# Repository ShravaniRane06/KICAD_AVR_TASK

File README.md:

# KICAD_AVR_TASK
AVR Atmega328 IPD Task1
PCB AND SCHEMATIC

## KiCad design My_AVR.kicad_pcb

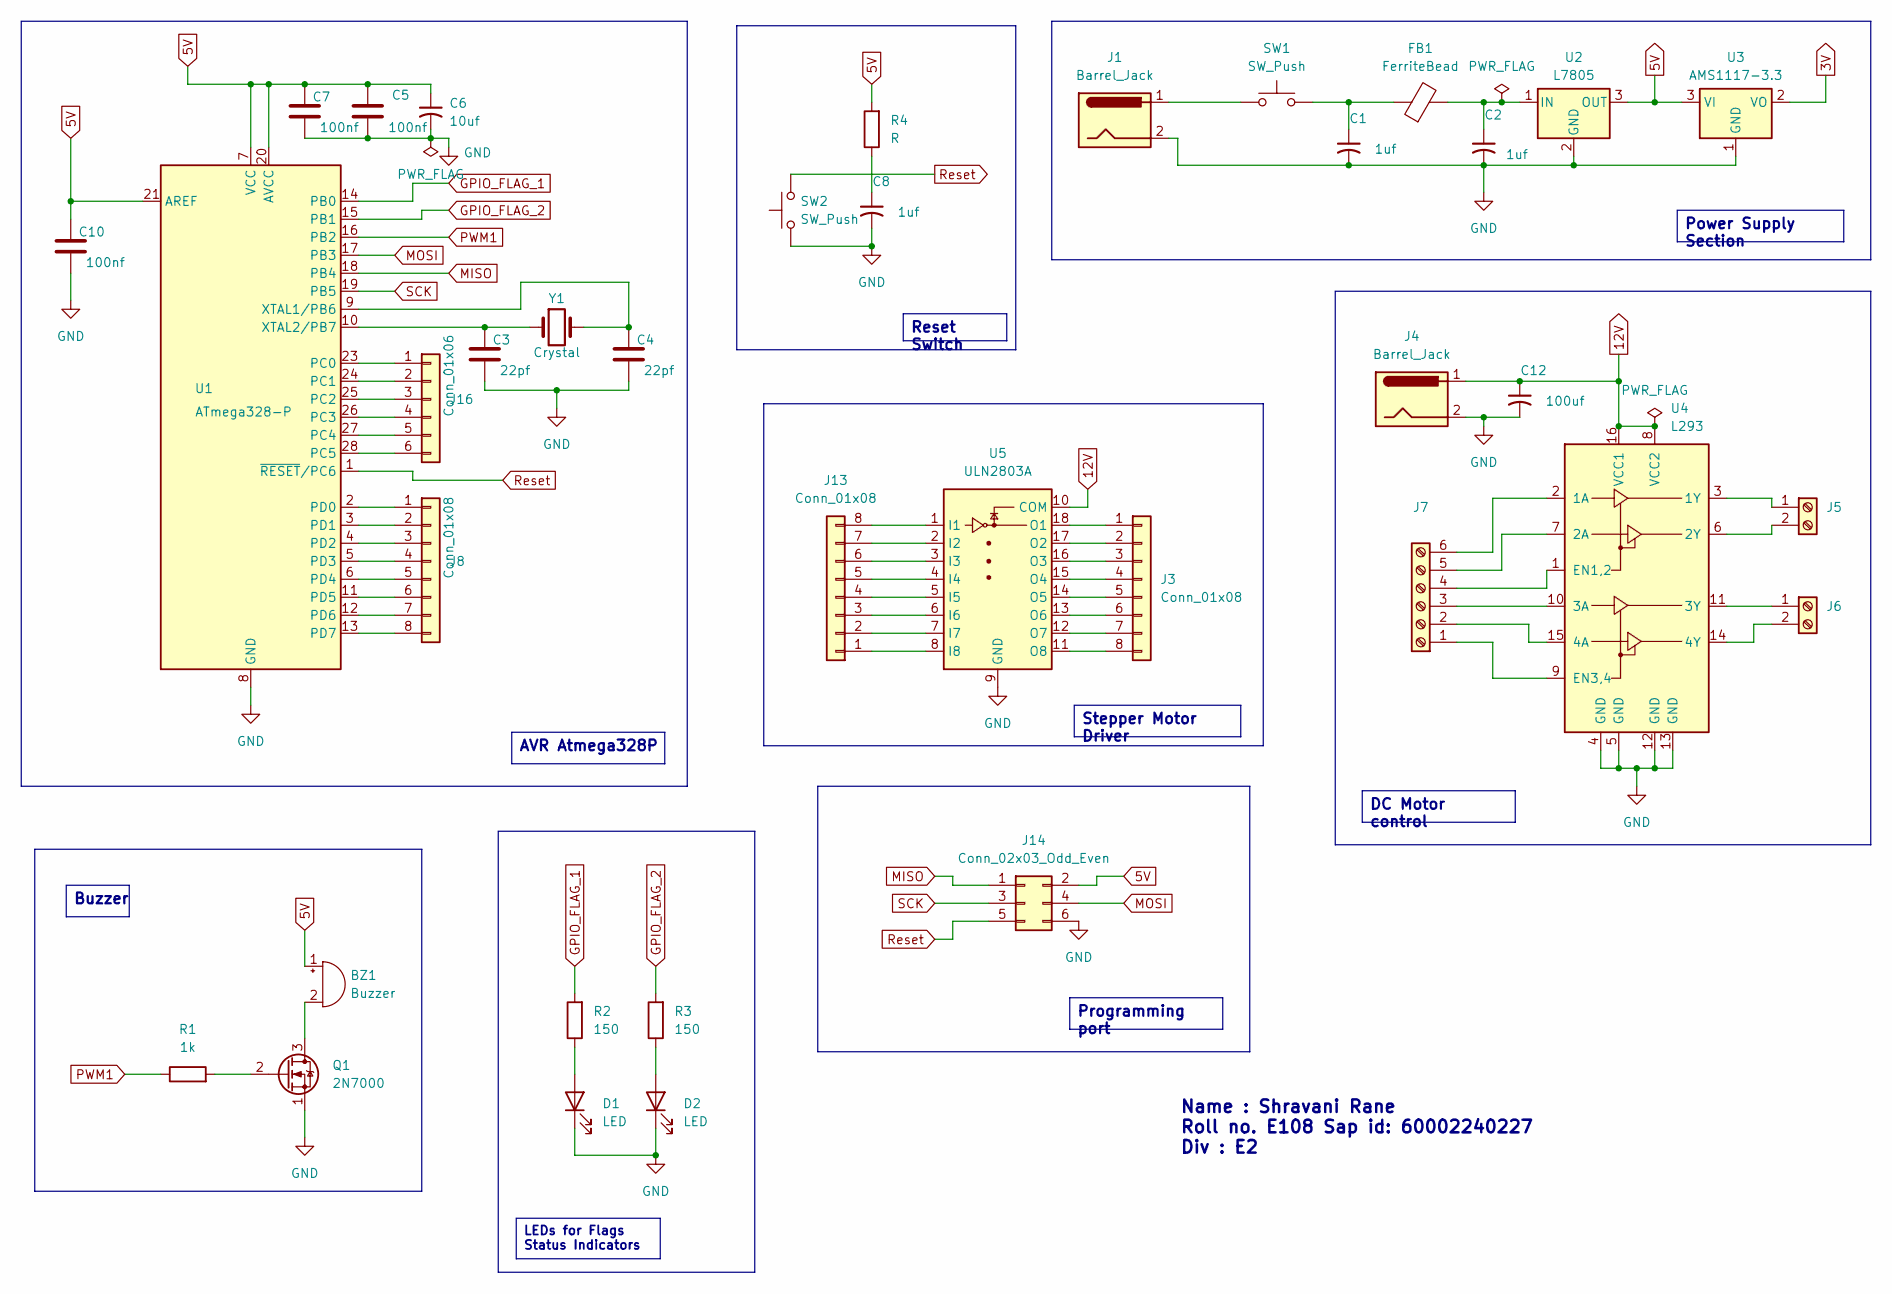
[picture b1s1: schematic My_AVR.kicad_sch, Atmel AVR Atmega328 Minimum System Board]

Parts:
BZ1: Buzzer; Buzzer_12x9.5RM7.6
C1, C2, C8: 1uf; CP_Radial_D5.0mm_P2.50mm
C3, C4: 22pf; C_0805_2012Metric
C5, C7, C10: 100nf; C_1206_3216Metric
C6: 10uf; CP_Radial_D4.0mm_P2.00mm
C12: 100uf; C_1206_3216Metric
D1, D2: LED; LED_D3.0mm_Clear
FB1: FerriteBead; LairdTech_28C0236-0JW-10
J1, J4: Barrel_Jack; BarrelJack_Horizontal
J3, J8, J13: Conn_01x08; PinHeader_1x08_P2.54mm_Vertical
J5, J6: Screw_Terminal_01x02; TerminalBlock_Xinya_XY308-2.54-2P_1x02_P2.54mm_Horizontal
J7: Screw_Terminal_01x06; TerminalBlock_Xinya_XY308-2.54-6P_1x06_P2.54mm_Horizontal
J14: Conn_02x03_Odd_Even; PinHeader_2x03_P2.54mm_Vertical
J16: Conn_01x06; PinHeader_1x06_P2.54mm_Vertical
Q1: 2N7000; TO-92_Inline
R1: 1k; R_0805_2012Metric
R2, R3: 150; R_0805_2012Metric
R4: R; R_0805_2012Metric
SW1, SW2: SW_Push; SW_PUSH_6mm_H5mm
U1: ATmega328-P; DIP-28_W7.62mm
U2: L7805; TO-247-3_Vertical
U3: AMS1117-3.3; SOT-223-3_TabPin2
U4: L293; DIP-16_W7.62mm
U5: ULN2803A; DIP-20_W7.62mm
Y1: Crystal; Crystal_HC49-U_Horizontal

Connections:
3V: U3.2 (VO)
5V: BZ1.1 (+), C5.1, C6.1, C7.1, C10.1, J14.2, R4.2, U1.7 (VCC), U1.20 (AVCC), U1.21 (AREF), U2.3 (OUT), U3.3 (VI)
12V: C12.1, J4.1, U4.8 (VCC2), U4.16 (VCC1), U5.10 (COM)
GND: C1.2, C2.2, C3.2, C4.2, C5.2, C6.2, C7.2, C8.2, C10.2, C12.2, D1.1 (K), D2.1 (K), J1.2, J4.2, J14.6, Q1.1 (S), SW2.1, U1.8 (GND), U1.22 (GND), U2.2 (GND), U3.1 (GND), U4.4 (GND), U4.5 (GND), U4.12 (GND), U4.13 (GND), U5.9 (GND)
GPIO_FLAG_1: R2.2, U1.14 (PB0)
GPIO_FLAG_2: R3.2, U1.15 (PB1)
MISO: J14.1, U1.18 (PB4)
MOSI: J14.4, U1.17 (PB3)
unnamed: BZ1.2 (-), Q1.3 (D)
unnamed: C1.1, FB1.1, SW1.2
unnamed: C8.1, R4.1
unnamed: D1.2 (A), R2.1
unnamed: D2.2 (A), R3.1
unnamed: J1.1, SW1.1
unnamed: J3.1, U5.18 (O1)
unnamed: J3.2, U5.17 (O2)
unnamed: J3.3, U5.16 (O3)
unnamed: J3.4, U5.15 (O4)
unnamed: J3.5, U5.14 (O5)
unnamed: J3.6, U5.13 (O6)
unnamed: J3.7, U5.12 (O7)
unnamed: J3.8, U5.11 (O8)
unnamed: J5.1, U4.3 (1Y)
unnamed: J5.2, U4.6 (2Y)
unnamed: J6.1, U4.11 (3Y)
unnamed: J6.2, U4.14 (4Y)
unnamed: J7.1, U4.9 (EN3,4)
unnamed: J7.2, U4.15 (4A)
unnamed: J7.3, U4.10 (3A)
unnamed: J7.4, U4.1 (EN1,2)
unnamed: J7.5, U4.7 (2A)
unnamed: J7.6, U4.2 (1A)
unnamed: J8.1, U1.2 (PD0)
unnamed: J8.2, U1.3 (PD1)
unnamed: J8.3, U1.4 (PD2)
unnamed: J8.4, U1.5 (PD3)
unnamed: J8.5, U1.6 (PD4)
unnamed: J8.6, U1.11 (PD5)
unnamed: J8.7, U1.12 (PD6)
unnamed: J8.8, U1.13 (PD7)
unnamed: J13.1, U5.8 (I8)
unnamed: J13.2, U5.7 (I7)
unnamed: J13.3, U5.6 (I6)
unnamed: J13.4, U5.5 (I5)
unnamed: J13.5, U5.4 (I4)
unnamed: J13.6, U5.3 (I3)
unnamed: J13.7, U5.2 (I2)
unnamed: J13.8, U5.1 (I1)
unnamed: J16.1, U1.23 (PC0)
unnamed: J16.2, U1.24 (PC1)
unnamed: J16.3, U1.25 (PC2)
unnamed: J16.4, U1.26 (PC3)
unnamed: J16.5, U1.27 (PC4)
unnamed: J16.6, U1.28 (PC5)
unnamed: Q1.2 (G), R1.2
unnamed: C4.1, U1.9 (XTAL1/PB6), Y1.2
unnamed: C3.1, U1.10 (XTAL2/PB7), Y1.1
unnamed: C2.1, FB1.2, U2.1 (IN)
PWM1: R1.1, U1.16 (PB2)
Reset: J14.5, SW2.2, U1.1 (~RESET/PC6)
SCK: J14.3, U1.19 (PB5)

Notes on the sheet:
Name : Shravani Rane Roll no. E108 Sap id: 60002240227 Div : E2
Buzzer
Programming port
DC Motor control
AVR Atmega328P
Power Supply Section
LEDs for Flags Status Indicators
Reset Switch
Stepper Motor Driver

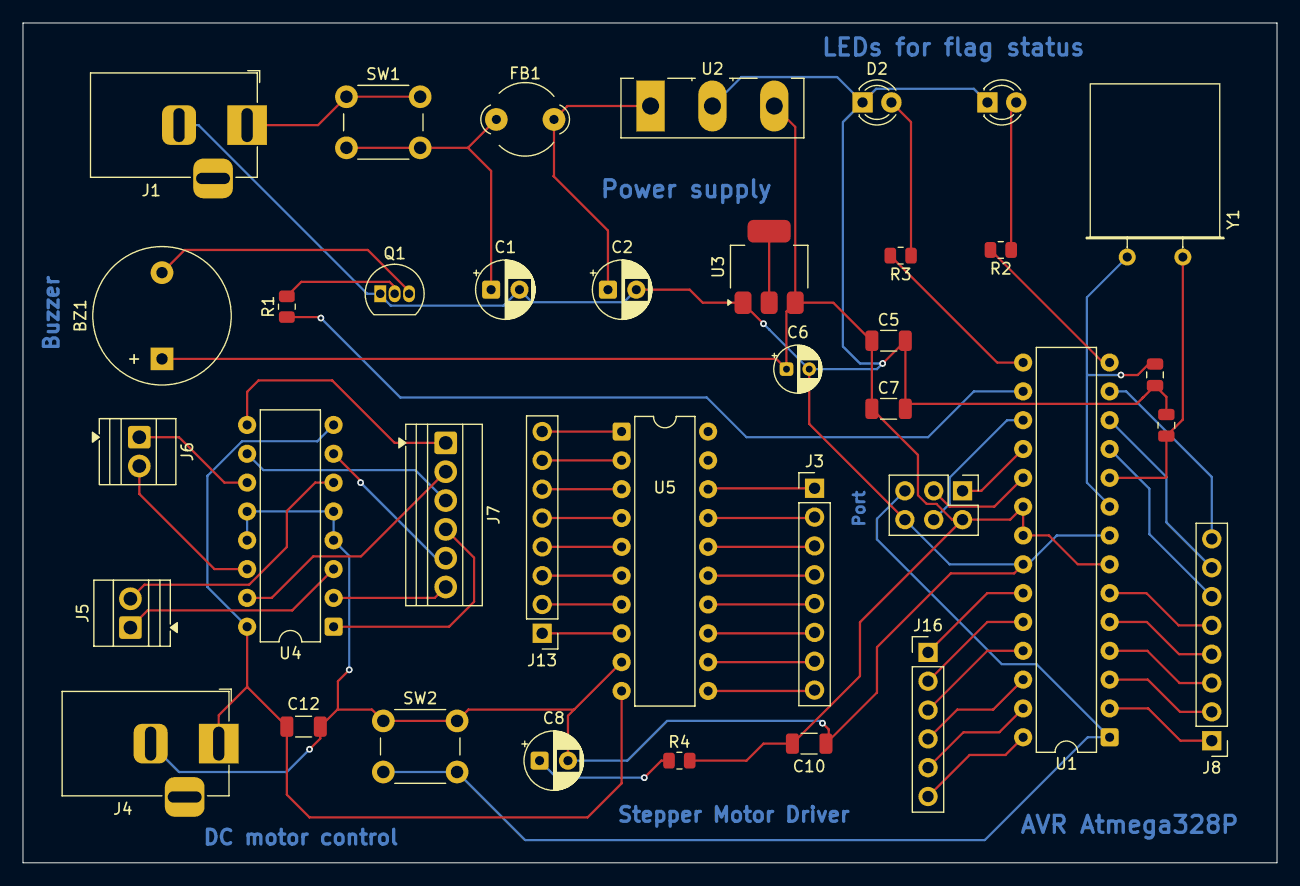
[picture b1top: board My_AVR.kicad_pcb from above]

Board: 2 copper layers, 110.5 x 74.0 mm, 37 parts (0 on the bottom side), 60 nets.
